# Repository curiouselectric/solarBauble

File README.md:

# Solar Bauble
Solar powered flashing Christmas ornament design files and firmware. 
Based on ATTiny85 micro-controller.

Kit available to purchase here:

[https://www.curiouselectric.co.uk/products/solar-bauble-solar-powered-festive-diy-decoration](https://www.curiouselectric.co.uk/products/solar-bauble-solar-powered-festive-diy-decoration)

Files include:

* PCB design files (KiCAD)
* Instructions
* Firmware (Arduino IDE)

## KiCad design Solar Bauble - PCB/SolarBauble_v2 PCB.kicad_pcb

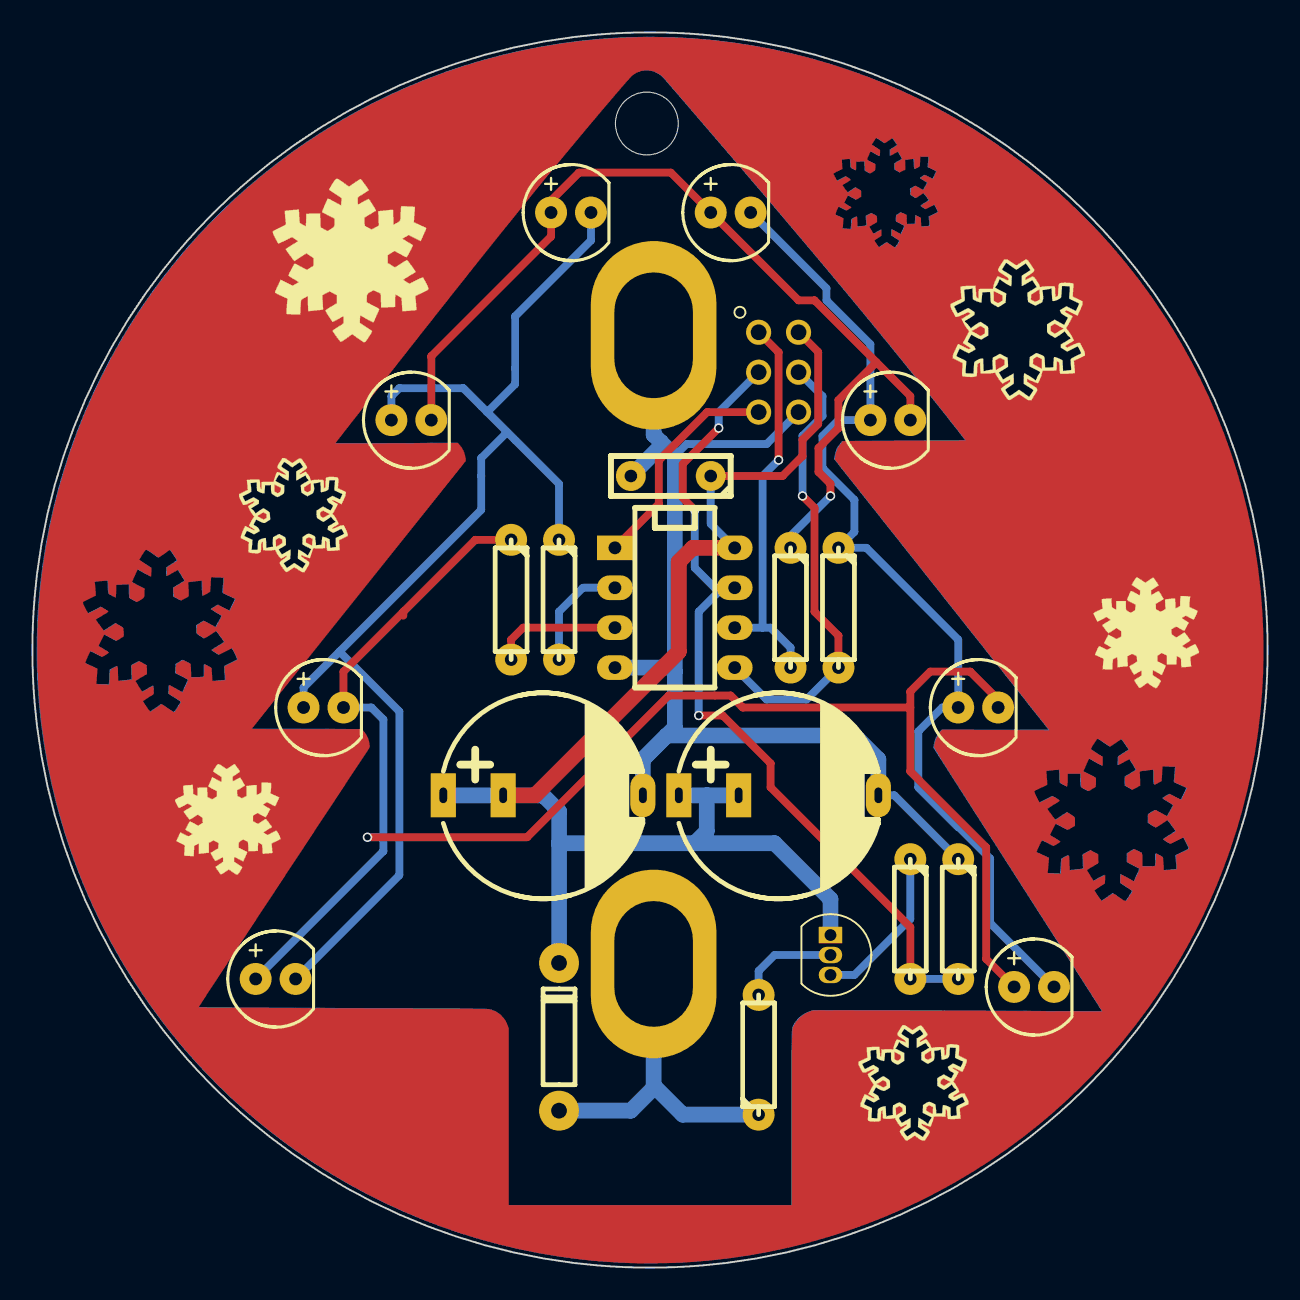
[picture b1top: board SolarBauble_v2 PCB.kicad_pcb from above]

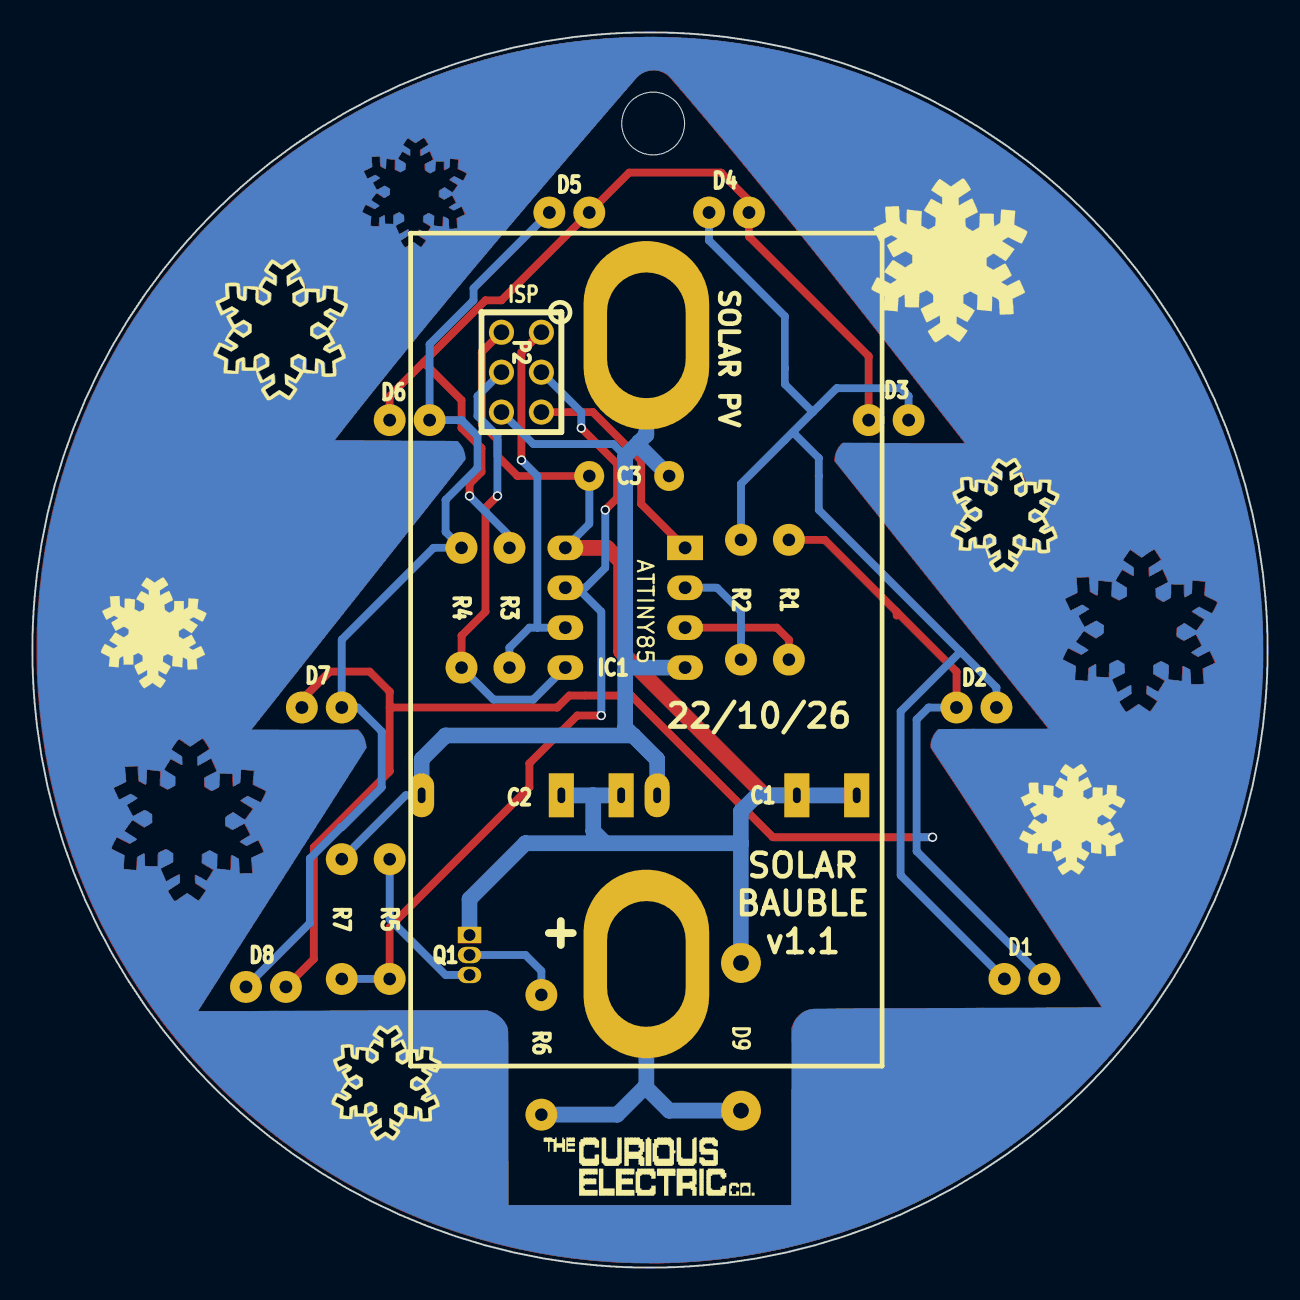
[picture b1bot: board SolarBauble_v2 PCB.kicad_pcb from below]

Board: 2 copper layers, 78.6 x 78.6 mm, 25 parts (2 on the bottom side), 15 nets.

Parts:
C1, C2: 0.47F; C_0_47F_SuperCap_2POS
C3: 100n; C1_wide_lg_pad_2
D1, D2, D3, D4, D5, D6, D7, D8: LED; LED-5MM_larg_pad
D9: 1N5819; TH_Diode_1_reversed
IC1: ATTINY85; DIP-8_300_ELL
P2: ISP; ISP_3x2
P4: HOLES; PCB_solarbauble_pcb_outline_tree_4_5
P7: LOGO2; TCEC_Words_13mm
Q1: 2N3906; TO-92_Inline
R1, R2, R3, R4: 1k; R3-LARGE_PADS_0_8_hole
R5: 100k; R3-LARGE_PADS_0_8_hole
R6, R7: 10k; R3-LARGE_PADS_0_8_hole
SC1: SOLAR PV; PV_53x30mm_Area

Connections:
/LED0: IC1.3 (PB4(XTAL2/CLKO/OC1B/ADC2/PCINT4)), R1.2
/LED1: IC1.2 (PB3(XTAL1/CLKI/OC1B/ADC3/PCINT3)), R2.2
/LED2: IC1.6 (PB1(MISO/DO/AIN1/OC0B/OC1A/PCINT1)), P2.1, R3.2
/LED3: IC1.5 (PB0(MOSI/DI/SDA/AIN0/OC0A/OC1A/AREF/PCI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), P2.4, R4.2
/PV+: D9.2 (A), R6.1, SC1.1 (+)
/SWITCH: IC1.7 (PB2(SCK/USCK/SCL/T0/INT0/ADC1/PCINT2)), P2.3, R5.2, R7.2
GND: C1.2, C2.2, C3.2, IC1.4 (GND), P2.6, R7.1, SC1.2 (-)
unnamed: D1.1 (A), D2.2 (K), D7.2 (K), D8.1 (A), R1.1
unnamed: D1.2 (K), D2.1 (A), D3.1 (A), D4.2 (K), R2.1
unnamed: D3.2 (K), D4.1 (A), D5.1 (A), D6.2 (K), R3.1
unnamed: D5.2 (K), D6.1 (A), D7.1 (A), D8.2 (K), R4.1
unnamed: IC1.1 (PB5(~RESET/dW/ADC0/PCINT5)), P2.5
unnamed: Q1.2 (B), R6.2
unnamed: Q1.3 (C), R5.1
VCC: C1.1, C2.1, C3.1, D9.1 (K), IC1.8 (VCC), P2.2, Q1.1 (E)

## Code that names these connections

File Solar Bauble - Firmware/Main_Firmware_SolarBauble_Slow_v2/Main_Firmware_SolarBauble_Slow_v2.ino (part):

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#include <avr/interrupt.h>

// Pin Assignments
#define pinLED0 PB0  // Pin 5 on ATtiny85
#define pinLED1 PB1  // Pin 6 on ATtiny85
#define pinLED2 PB3  // Pin 2 on ATtiny85
#define pinLED3 PB4  // Pin 3 on ATtiny85
#define sw PB2       // Pin 7 on ATtiny85 (Analog Input A1)

// Configuration Parameters
// ADC Thresholds mapped via 100k/10k divider to 1.1V Internal Ref
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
